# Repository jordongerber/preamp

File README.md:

# Preamp

## Goals

 * Learn Kicad
 * Become familiar with microcontroller programming
  * SPI
  * Shift registers
  * Mux/Demux
  * Controller interrupts
 * Make a bomb preamp
  * See the block diagram in [/preamp-layout/](https://github.com/SlurpyTurts/preamp/tree/master/preamp-layout) for details of the overall design.

## Implementation
* I am planning to use an ESP32 controller as the MCU
* This preamp will implement relay-controlled input and output switching
  * Inputs
    * Some number of single-ended RCA pairs
 	  * 1-2 pairs balanced pairs
    * relays controlled via demux from MCU. Input control via
      * Front panel rotary encoder
      * Front panel capacitive touch sensors
      * IR remote control
      * Because it's an ESP32, I gotta play with network control
 		* Selection remembered when the device is power-cycled
 	* Outputs
 		* 1x single-ended RCA pair
 		* 1x balanced XLR pair
 		* Headphone Amp
 			* Op-amp driven amp will have single-ended output.
 			* Preamp main outputs will be muted when the headphone amp has a device inserted
 			* When headphones are inserted the previous headphone level will be retained
 			* When headphones are unplugged the main output volume will be retained from before insertion
 		* Upon bootup the headphone volume will come in low (previous state not remembered) but not off, TBD
 * Volume control will be implemented via an MDAC controller
 * Selectable gain setting: 0dB or +12dB
 * Power Supply
 	* Separate linear power supplies for analog and digital sections
 		* 5V
 		* +-15V
 * Headphone Amp
 	* Single-ended Op-amp design
 * Tone Controls
 	* Meh. At the moment I don't really care about tone controls on this unit. If I do add them I'd like to have:
 		* Low/high pass loudness controls w/ controllable corner frequency
 		* Parametric upper-midrange control, 2kHz - 5kHz, variable Q, variable gain (-6dB to 0dB)
 		* Parametric lower-midrange control, 200Hz - 500kHz, variable Q, variable gain (-6dB to +2dB)  

## Instructions

* The files in [/preamp-code](https://github.com/SlurpyTurts/preamp/tree/master/preamp-code) can be run in the Arduino IDE. Currently it is configured for an ESP32.
* The schematic & pcb files in [/preamp-layout/preamp-kicad](https://github.com/SlurpyTurts/preamp/tree/master/preamp-layout/preamp-kicad) can be viewed using KiCad. Open the file ```preamp.pro```
* An overview of the schematic layout of this preamp is located at [preamp/preamp-layout/preamp-kicad/preamp.pdf](https://github.com/SlurpyTurts/preamp/blob/master/preamp-layout/preamp-kicad/preamp.pdf)

## References

### Preamp design
 * https://github.com/FutureSharks/preamp-two
 * https://www.muffsy.com/muffsy-relay-input-selector-4.html
 * https://sound-au.com/articles/balanced-io.htm
 * http://www.interfacebus.com/tone-control-3-band-tlo82-opamp-design.html
 * http://www.thatcorp.com/2181-series_Trimmable_Blackmer_IC_Voltage-Controlled_Amplifiers.shtml

### Power Supply design
 * https://www.eleccircuit.com/dual-adjustable-power-supply-circuit-diagram/

### SPI
 * SPI - http://www.circuitbasics.com/basics-of-the-spi-communication-protocol/
 * shift registers for mux - https://www.brainy-bits.com/get-more-inputs-on-your-arduino-by-using-a-shift-register/
 * https://github.com/espressif/arduino-esp32/blob/master/libraries/SPI/examples/SPI_Multiple_Buses/SPI_Multiple_Buses.ino
 * https://github.com/espressif/arduino-esp32/issues/1942
 * https://github.com/MajenkoLibraries/MCP23S17

### Arduino
  * encoder interrupts - http://bristolwatch.com/arduino/arduino2.htm
  * encoder interrupts - https://www.arduino.cc/reference/en/language/functions/external-interrupts/attachinterrupt/
  * flash memory - https://randomnerdtutorials.com/esp32-flash-memory/

### Other
 * Neopixel - https://www.adafruit.com/product/3094

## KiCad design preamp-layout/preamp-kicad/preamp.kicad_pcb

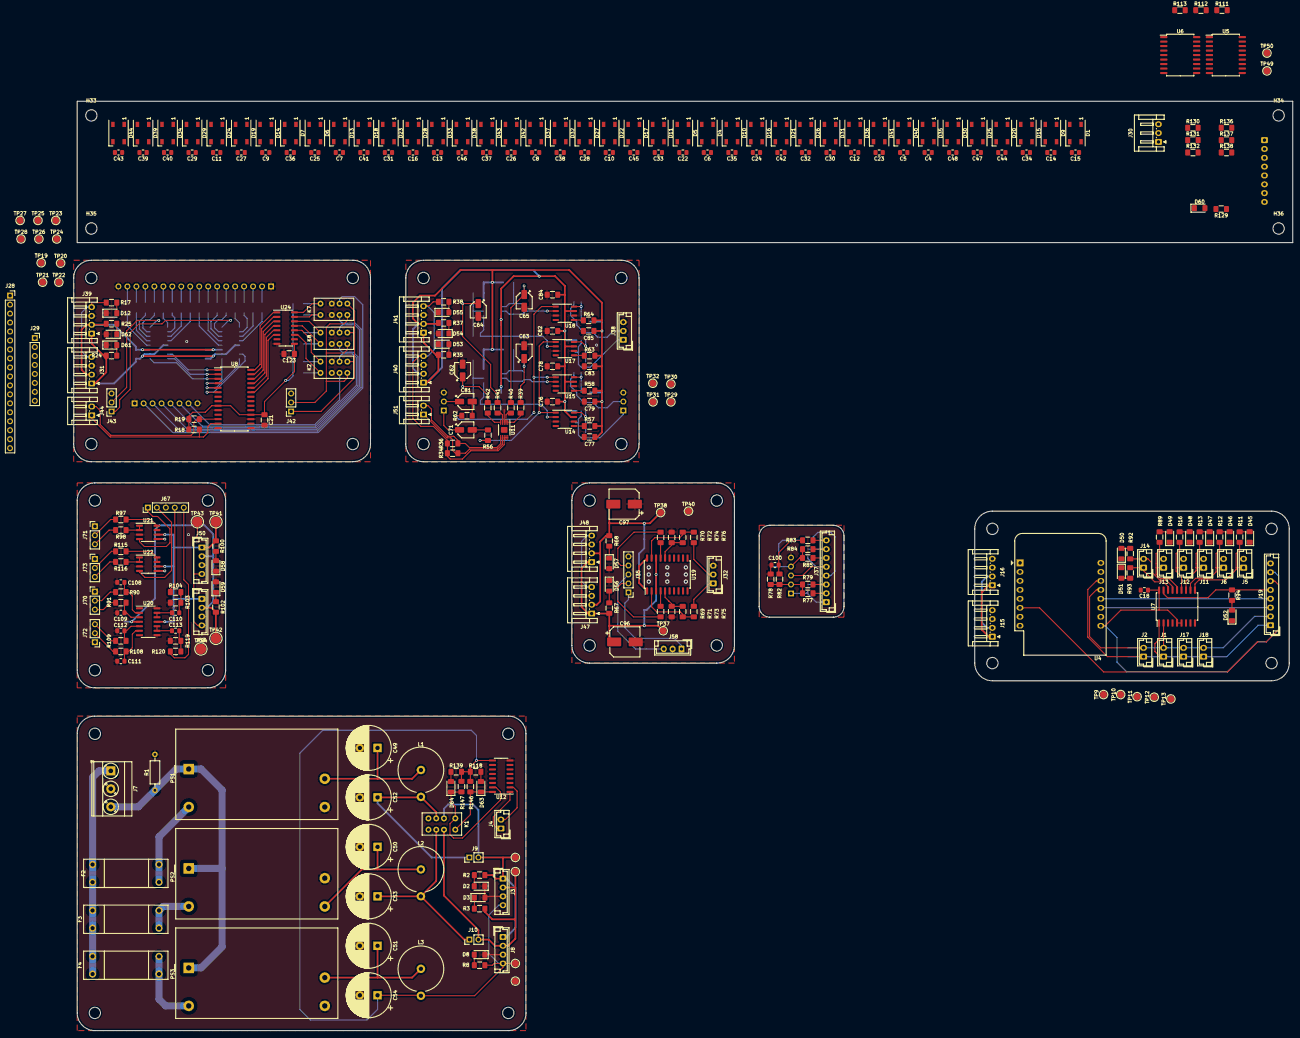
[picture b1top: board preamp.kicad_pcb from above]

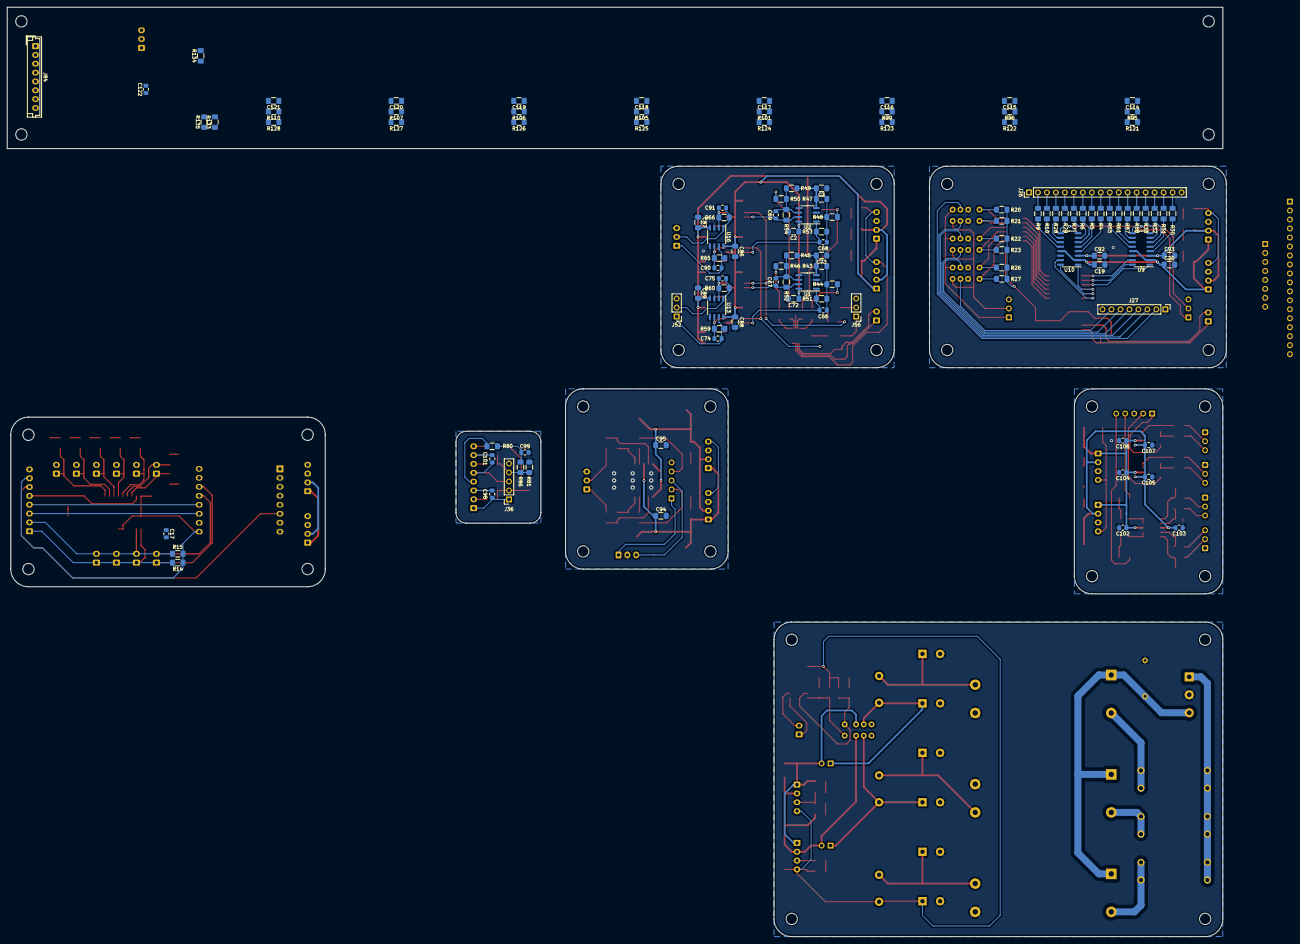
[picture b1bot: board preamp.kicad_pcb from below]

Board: 2 copper layers, 345.0 x 263.0 mm, 461 parts (115 on the bottom side), 245 nets.

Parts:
C2, C3, C19, C20, C21, C72, C73, C76, C77, C78, C79, C82, C83, C84, C85, C86, C87, C88, C89, C92, C93, C94, C95, C114, C115, C116, C117, C118, C119, C120, C121, C123: 0.1uF; C_1206_3216Metric_Pad1.42x1.75mm_HandSolder
C4, C5, C6, C7, C8, C9, C10, C11, C12, C13, C14, C15, C16, C22, C23, C24, C25, C26, C27, C28, C29, C30, C31, C32, C33, C34, C35, C36, C37, C38, C39, C40, C41, C42, C43, C44, C45, C46, C47, C48: 100nF; C_0805_2012Metric_Pad1.15x1.40mm_HandSolder
C17, C18, C66, C67, C68, C69, C102, C103, C104, C105, C106, C107, C122: 0.1uF; C_0805_2012Metric_Pad1.15x1.40mm_HandSolder
C49, C50, C51, C52, C53, C54: 470uF; CP_Radial_D12.5mm_P5.00mm
C62, C63, C64, C65: 2.2uF; CP_Elec_4x5.4
C71, C81: 10uF; CP_Elec_4x5.4
C74, C75, C90, C91: 22pF; C_0805_2012Metric_Pad1.15x1.40mm_HandSolder
C96, C97: 100uF; CP_Elec_8x6.2
C98, C101: 0.022uF; C_0805_2012Metric_Pad1.15x1.40mm_HandSolder
C99, C100: 0.12uF; C_0805_2012Metric_Pad1.15x1.40mm_HandSolder
C108, C109, C111, C112: 470pF; C_0805_2012Metric_Pad1.15x1.40mm_HandSolder
C110, C113: 22uF; C_0805_2012Metric_Pad1.15x1.40mm_HandSolder
D1, D4, D5, D6, D7, D9, D10, D11, D13, D14, D15, D16, D17, D18, D19, D20, D21, D22, D23, D24, D25, D26, D27, D28, D29, D30, D31, D32, D33, D34, D35, D36, D37, D38, D39, D40, D41, D42, D43, D44: WS2812B; LED_WS2812B_PLCC4_5.0x5.0mm_P3.2mm
D2, D3, D53, D54, D56, D57, D58, D59, D61, D62: GREEN; LED_1206_3216Metric_Pad1.42x1.75mm_HandSolder
D8, D12, D45, D46, D47, D48, D49, D50, D51, D52, D55, D60, D63, D64: RED; LED_1206_3216Metric_Pad1.42x1.75mm_HandSolder
F2, F3, F4: 500mA; 01110501Z_3AG
H1, H2, H3, H4, H9, H10, H11, H12, H17, H18, H19, H20, H21, H22, H23, H24, H25, H26, H27, H28, H29, H30, H31, H32, H33, H34, H35, H36: MountingHole; MountingHole_3.2mm_M3
J1, J2, J4, J5, J6, J11, J12, J13, J14, J17, J18: Conn_01x02_Female; JST_EH_B2B-EH-A_1x02_P2.50mm_Vertical
J3, J8, J50, J53: Conn_01x04_Male; JST_EH_B4B-EH-A_1x04_P2.50mm_Vertical
J7: Screw_Terminal_01x03; TerminalBlock_Phoenix_MKDS-3-3-5.08_1x03_P5.08mm_Horizontal
J9, J10: Conn_01x02_Male; PinHeader_1x02_P2.54mm_Vertical
J15, J16, J31, J39, J40, J41, J47, J48: Conn_01x04_Male; JST_EH_S4B-EH_1x04_P2.50mm_Horizontal
J19, J84: Conn_01x08_Female; JST_EH_B8B-EH-A_1x08_P2.50mm_Vertical
J26: Conn_01x18_Male; PinHeader_1x18_P2.54mm_Vertical
J27: Conn_01x08_Male; PinHeader_1x08_P2.54mm_Vertical
J28: Conn_01x18_Female; PinSocket_1x18_P2.54mm_Vertical
J29: Conn_01x08_Female; PinSocket_1x08_P2.54mm_Vertical
J30: Conn_01x03_Female; JST_EH_S3B-EH_1x03_P2.50mm_Horizontal
J32, J38, J58: Conn_01x03_Male; JST_EH_B3B-EH-A_1x03_P2.50mm_Vertical
J35, J67: Conn_01x05_Male; PinHeader_1x05_P2.54mm_Vertical
J36: Conn_01x05_Female; PinSocket_1x05_P2.54mm_Vertical
J37: Conn_01x08_Male; JST_EH_B8B-EH-A_1x08_P2.50mm_Vertical
J42, J43: Conn_01x03_Female; PinSocket_1x03_P2.54mm_Vertical
J44: Conn_01x02_Female; JST_EH_S2B-EH_1x02_P2.50mm_Horizontal
J51: Conn_01x02_Male; JST_EH_S2B-EH_1x02_P2.50mm_Horizontal
J52, J56: Conn_01x03_Male; PinHeader_1x03_P2.54mm_Vertical
J70, J71, J72, J73: XLR3; PinHeader_1x03_P2.54mm_Vertical
K1, K2, K7, K8: G6JU; Relay_DPDT_Omron_G6JU-2P-Y
L1, L2, L3: 150uH; L_Axial_L23.4mm_D12.7mm_P7.62mm_Vertical_Vishay_IHA-203
PS1, PS2: IRM-10-15; Converter_ACDC_MeanWell_IRM-10-xx_THT
PS3: IRM-05-5; Converter_ACDC_MeanWell_IRM-05-xx_THT
R1: 4.7M; R_Axial_DIN0207_L6.3mm_D2.5mm_P10.16mm_Horizontal
R2, R3: 1.3k; R_1206_3216Metric_Pad1.42x1.75mm_HandSolder
R4, R5, R6, R7, R9, R10, R28, R29, R30, R31, R32, R33, R55, R61, R87, R88, R90, R91, R97, R98, R104, R108, R109, R115, R116, R120, R121, R122, R123, R124, R125, R126, R127, R128: 100R; R_1206_3216Metric_Pad1.42x1.75mm_HandSolder
R8, R11, R12, R13, R16, R17, R38, R89, R92, R93, R94, R118, R129, R139: 330R; R_1206_3216Metric_Pad1.42x1.75mm_HandSolder
R14, R15, R18, R19, R24, R25, R34, R35, R36, R37, R67, R68, R77, R85, R100, R102, R111, R113, R133, R135: 1.5k; R_1206_3216Metric_Pad1.42x1.75mm_HandSolder
R20, R21, R22, R23, R26, R27, R69, R70, R146, R147: 51R; R_1206_3216Metric_Pad1.42x1.75mm_HandSolder
R39, R40, R41, R42: 6.34k; R_1206_3216Metric_Pad1.42x1.75mm_HandSolder
R43, R45, R47, R49: 178k; R_1206_3216Metric_Pad1.42x1.75mm_HandSolder
R44, R46, R48, R50: 6.49k; R_1206_3216Metric_Pad1.42x1.75mm_HandSolder
R51, R52, R53, R54: 2k; R_1206_3216Metric_Pad1.42x1.75mm_HandSolder
R56, R59, R60, R62, R65, R66: 20k; R_1206_3216Metric_Pad1.42x1.75mm_HandSolder
R57, R58, R63, R64: 5.1k; R_1206_3216Metric_Pad1.42x1.75mm_HandSolder
R71, R72, R73, R74, R78, R86, R130, R131, R132, R136, R137, R138: 1k; R_1206_3216Metric_Pad1.42x1.75mm_HandSolder
R75, R76: 10R; R_1206_3216Metric_Pad1.42x1.75mm_HandSolder
R79, R84: 9.1k; R_1206_3216Metric_Pad1.42x1.75mm_HandSolder
R80, R81, R82, R83: 3.3k; R_1206_3216Metric_Pad1.42x1.75mm_HandSolder
R95, R96, R99, R101, R105, R106, R107, R110: 1M; R_1206_3216Metric_Pad1.42x1.75mm_HandSolder
R103, R119: 100k; R_1206_3216Metric_Pad1.42x1.75mm_HandSolder
R112, R134: 10k; R_1206_3216Metric_Pad1.42x1.75mm_HandSolder
TP9, TP10, TP11, TP12, TP13, TP19, TP20, TP21, TP22, TP23, TP24, TP25, TP26, TP27, TP28, TP29, TP30, TP31, TP32, TP37, TP38, TP40, TP45, TP46, TP47, TP48, TP49, TP50: TestPoint; TestPoint_Pad_D2.0mm
TP41, TP42, TP43, TP44: TestPoint; TestPoint_Pad_D3.0mm
U1, U2: TL072; SOIC-8_3.9x4.9mm_P1.27mm
U4: WeMos_D1_mini; WEMOS_D1_mini_light
U5, U6, U7: MCP23008T-E_SO; SOIC-18W_7.5x11.6mm_P1.27mm
U8: MCP23017_SO; SOIC-28W_7.5x17.9mm_P1.27mm
U9, U10: DG408DY; SOIC-16_3.9x9.9mm_P1.27mm
U11: DAC5574; MSOP-10-1EP_3x3mm_P0.5mm_EP1.68x1.88mm
U12, U24: ULN2003; SOIC-16_3.9x9.9mm_P1.27mm
U13, U16: NJM2068M; SOP-8_3.9x4.9mm_P1.27mm
U14, U15, U17, U18: THAT2181; SO-8_3.9x4.9mm_P1.27mm
U19: TPA6120; SOIC-20W_7.5x12.8mm_P1.27mm
U20: THAT1280; SOIC-14_3.9x8.7mm_P1.27mm
U21, U22: THAT1646; SOIC-8_3.9x4.9mm_P1.27mm

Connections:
+3.3V: C17.1, TP12.1, U4.8
+5V: C4.1, C5.2, C6.1, C7.2, C8.1, C9.2, C10.1, C11.2, C12.1, C13.2, C14.1, C15.2, C16.1, C18.1, C21.1, C22.2, C23.1, C24.2, C25.1, C26.2, C27.1, C28.2, C29.1, C30.2, C31.1, C32.2, C33.1, C34.2, C35.1, C36.2, C37.1, C38.2, C39.1, C40.2, C41.1, C42.2, C43.1, C44.2, C45.1, C46.2, C47.1, C48.2, C54.1, C122.1, C123.1, D1.1, D4.1, D5.1, D6.1, D7.1, D9.1, D10.1, D11.1, D13.1, D14.1, D15.1, D16.1, D17.1, D18.1, D19.1, D20.1, D21.1, D22.1, D23.1, D24.1, D25.1, D26.1, D27.1, D28.1, D29.1, D30.1, D31.1, D32.1, D33.1, D34.1, D35.1, D36.1, D37.1, D38.1, D39.1, D40.1, D41.1, D42.1, D43.1, D44.1, J3.4, J8.4, J15.4, J16.4, J19.7, J30.1, J31.4, J39.4, J40.4, J41.4, J47.4, J48.4, J50.4, J53.4, J84.7, L3.2, R8.1, R14.1, R15.1, R17.1, R18.1, R19.1, R20.1, R21.1, R22.1, R23.1, R26.1, R27.1, R34.1, R36.1, R38.1, R95.2, R96.2, R99.2, R101.2, R105.2, R106.2, R107.2, R110.2, R111.1, R113.1, R118.1, R129.1, R130.1, R131.1, R132.1, R133.1, R135.1, R136.1, R137.1, R138.1, R139.1, R146.1, R147.1, TP11.1, TP21.1, TP31.1, TP43.1, TP47.1, TP49.1, U4.9, U5.18, U6.3, U6.18, U7.5, U7.6, U7.18, U8.9, U8.16, U8.18, U11.8, U11.9, U11.10, U12.9, U24.9
+15V: C2.1, C19.1, C20.1, C72.1, C76.1, C78.1, C82.1, C84.1, C86.1, C88.1, C94.1, C96.1, C102.1, C104.1, C106.1, J3.1, J8.1, J9.2, J15.1, J16.1, J31.1, J39.1, J40.1, J41.1, J47.1, J48.1, J50.1, J53.1, K1.7, R2.1, R24.2, R35.1, R67.1, R100.1, TP9.1, TP19.1, TP29.1, TP37.1, TP41.1, TP45.1, U1.8, U2.8, U9.2, U9.13, U10.2, U10.13, U13.8, U14.7, U15.7, U16.8, U17.7, U18.7, U19.3, U19.18, U20.11, U21.6, U22.6
-15V: C3.2, C73.2, C77.2, C79.2, C83.2, C85.2, C87.2, C89.2, C92.1, C93.1, C95.1, C97.2, C103.2, C105.2, C107.2, J3.2, J8.2, J10.2, J15.2, J16.2, J31.2, J39.2, J40.2, J41.2, J47.2, J48.2, J50.2, J53.2, K1.2, R3.1, R25.1, R37.1, R43.2, R45.2, R47.2, R49.2, R57.2, R58.2, R63.2, R64.2, R68.1, R102.1, TP10.1, TP20.1, TP30.1, TP38.1, TP42.1, TP46.1, U1.4, U2.4, U9.3, U10.3, U13.4, U16.4, U19.1, U19.20, U20.4, U21.5, U22.5
/DC_PWR SUPPLY/+15: C52.1, J9.1, K1.6, L1.2
/DC_PWR SUPPLY/-15: C53.1, J10.1, K1.3, L2.2
/DC_PWR SUPPLY/AC_HOT: F2.2, F3.2, F4.2, J7.1
/DC_PWR SUPPLY/AC_N: J7.3, PS1.1, PS2.1, PS3.1, R1.1
/DC_PWR SUPPLY/STBY_CTRL_1: D63.1, K1.1, R146.2, U12.16
/DC_PWR SUPPLY/STBY_CTRL_2: D64.1, K1.8, R147.2, U12.15
/DC_PWR SUPPLY/STBY_RST: J4.2, J14.1, R93.1, U7.16, U12.2
/DC_PWR SUPPLY/STBY_SET: J4.1, J14.2, R92.1, U7.15, U12.1
/IO/A_IN_1_L: J26.2, J28.2, R9.2
/IO/A_IN_1_R: J26.10, J28.10, R55.2
/IO/A_IN_2_L: J26.3, J28.3, R10.2
/IO/A_IN_2_R: J26.11, J28.11, R61.2
/IO/A_IN_3_L: J26.4, J28.4, R28.2
/IO/A_IN_3_R: J26.12, J28.12, R87.2
/IO/A_IN_4_L: J26.5, J28.5, R29.2
/IO/A_IN_4_R: J26.13, J28.13, R88.2
/IO/A_IN_5_L: J26.6, J28.9, J67.4, R7.2, R104.1
/IO/A_IN_5_R: J26.14, J28.17, J67.5, R33.2, R120.1
/IO/A_OUT_1_L: J27.2, J29.2, K7.3
/IO/A_OUT_1_R: J27.3, J29.3, K7.6
/IO/A_OUT_2_L: J27.4, J29.4, J67.1, K8.3, U21.4
/IO/A_OUT_2_R: J27.5, J29.5, J67.2, K8.6, U22.4
/MCU/ENC_INT: J19.3, J84.4, U4.11, U6.8
/MCU/GP0: J5.1, R11.1, U7.10
/MCU/GP1: J6.1, R12.1, U7.11
/MCU/GP2: J11.1, R13.1, U7.12
/MCU/GP3: J12.1, R16.1, U7.13
/MCU/GP4: J13.1, R89.1, U7.14
/MCU/~FP_RST: J19.5, J84.5, R94.1, R112.2, R134.2, U7.17
/SCL: J1.1, J2.1, J17.1, J18.1, J19.1, J44.2, J51.2, J84.2, R14.2, R19.2, R36.2, R113.2, R135.2, U4.14, U5.2, U6.2, U7.1, U8.12, U11.6
/SDA: J1.2, J2.2, J17.2, J18.2, J19.2, J44.1, J51.1, J84.1, R15.2, R18.2, R34.2, R111.2, R133.2, U4.13, U5.1, U6.1, U7.2, U8.13, U11.7
/Volume Control/A_IN_L: R56.1, U14.1, U17.1
/Volume Control/A_IN_R: R62.1, U15.1, U18.1
/Volume Control/DAC_A: R39.2, U11.1
/Volume Control/DAC_B: R40.2, U11.2
/Volume Control/DAC_C: R41.2, U11.4
/Volume Control/DAC_D: R42.2, U11.5
/Volume Control/GAIN_CTRL_1_L: C68.1, R53.1, U2.1, U17.2
/Volume Control/GAIN_CTRL_1_R: C69.1, R54.1, U2.7, U18.2
/Volume Control/GAIN_CTRL_2_L: C66.1, R51.1, U1.1, U14.2
/Volume Control/GAIN_CTRL_2_R: C67.1, R52.1, U1.7, U15.2
/front panel/FP_INT_SW: J19.4, J84.3, U4.12, U5.8
/front panel/FP_LED_DT: D1.4, J19.6, J30.2, J84.6, U4.6
/front panel/SEL_CLK: R131.2, U6.10
/front panel/SEL_DT: R130.2, U6.11
/front panel/SEL_SW: R132.2, U6.12
/front panel/SW_IN_1: R121.2, U5.10
/front panel/SW_IN_2: R122.2, U5.11
/front panel/SW_IN_3: R123.2, U5.12
/front panel/SW_IN_4: R124.2, U5.13
/front panel/SW_IN_5: R125.2, U5.14
/front panel/SW_MUTE: R126.2, U5.15
/front panel/SW_OUT_1: R127.2, U5.16
/front panel/SW_OUT_2: R128.2, U5.17
/front panel/VOL_CLK: R137.2, U6.13
/front panel/VOL_DT: R136.2, U6.14
/front panel/VOL_SW: R138.2, U6.15
/headphone amp/Headphone Crossfeed/SW_L_OUT_1: C98.2, J37.3, R79.1
/headphone amp/Headphone Crossfeed/SW_L_OUT_2: J37.4, R80.1
/headphone amp/Headphone Crossfeed/SW_R_OUT_1: C101.2, J37.7, R84.1
/headphone amp/Headphone Crossfeed/SW_R_OUT_2: J37.8, R83.1
/headphone amp/Headphone Crossfeed/VR_L_OUT: J37.2, R77.1
/headphone amp/Headphone Crossfeed/VR_R_OUT: J37.6, R85.1
/headphone amp/IN_L: C90.1, C98.1, J35.1, J36.1, J37.1, J38.1, J58.1, R65.1, U16.7
/headphone amp/IN_R: C91.1, C101.1, J35.3, J36.3, J37.5, J38.2, J58.3, R66.1, U16.1
/headphone amp/OUT_L: J32.1, R75.1
/headphone amp/OUT_R: J32.2, R76.1
/headphone amp/xfeed_out_l: J35.2, J36.2, R69.2, R77.2, R78.1, R79.2, R82.2
/headphone amp/xfeed_out_r: J35.4, J36.4, R70.2, R81.2, R84.2, R85.2, R86.1
/input selector/A_IN_6_L: J26.7, R6.2
/input selector/A_IN_6_R: J26.15, R32.2
/input selector/A_IN_7_L: J26.8, R5.2
/input selector/A_IN_7_R: J26.16, R31.2
/input selector/A_IN_8_L: J26.9, R4.2
/input selector/A_IN_8_R: J26.17, R30.2
/input selector/A_IN_L: C74.1, J42.1, J52.1, K2.4, K7.4, K8.4, R59.1, U13.7
/input selector/A_IN_R: C75.1, J42.2, J52.2, K2.5, K7.5, K8.5, R60.1, U13.1
/input selector/A_OUT_3_L: J27.6, K2.3
/input selector/A_OUT_3_R: J27.7, K2.6
/input selector/A_OUT_L: C71.1, J43.1, J56.1, U10.8
/input selector/A_OUT_R: C81.1, J43.2, J56.2, U9.8
/input selector/IN_L_SEL_A0: TP23.1, U8.4, U10.1
/input selector/IN_L_SEL_A1: TP24.1, U8.5, U10.16
/input selector/IN_L_SEL_A2: TP25.1, U8.6, U10.15
/input selector/IN_R_SEL_A0: TP26.1, U8.3, U9.1
/input selector/IN_R_SEL_A1: TP27.1, U8.2, U9.16
/input selector/IN_R_SEL_A2: TP28.1, U8.1, U9.15
/input selector/OUT_1_R+: K7.8, R21.2, U24.15
/input selector/OUT_1_S+: K7.1, R20.2, U24.16
/input selector/OUT_2_R+: K8.8, R23.2, U24.13
/input selector/OUT_2_S+: K8.1, R22.2, U24.14
/input selector/OUT_3_R+: K2.8, R27.2, U24.11
/input selector/OUT_3_S+: K2.1, R26.2, U24.12
/input selector/RLY_1_R+: U8.27, U24.2
/input selector/RLY_1_S+: U8.28, U24.1
/input selector/RLY_2_R+: U8.25, U24.4
/input selector/RLY_2_S+: U8.26, U24.3
/input selector/RLY_3_R+: U8.23, U24.6
/input selector/RLY_3_S+: U8.24, U24.5
GND: C2.2, C3.1, C4.2, C5.1, C6.2, C7.1, C8.2, C9.1, C10.2, C11.1, C12.2, C13.1, C14.2, C15.1, C16.2, C17.2, C18.2, C19.2, C20.2, C21.2, C22.1, C23.2, C24.1, C25.2, C26.1, C27.2, C28.1, C29.2, C30.1, C31.2, C32.1, C33.2, C34.1, C35.2, C36.1, C37.2, C38.1, C39.2, C40.1, C41.2, C42.1, C43.2, C44.1, C45.2, C46.1, C47.2, C48.1, C49.2, C50.2, C51.2, C52.2, C53.2, C54.2, C62.2, C63.2, C64.2, C65.2, C72.2, C73.1, C76.2, C77.1, C78.2, C79.1, C82.2, C83.1, C84.2, C85.1, C86.2, C87.1, C88.2, C89.1, C92.2, C93.2, C94.2, C95.2, C96.2, C97.1, C99.2, C100.2, C102.2, C103.1, C104.2, C105.1, C106.2, C107.1, C108.2, C109.1, C111.2, C112.1, C114.2, C115.2, C116.2, C117.2, C118.2, C119.2, C120.2, C121.2, C122.2, C123.2, D1.3, D2.1, D3.2, D4.3, D5.3, D6.3, D7.3, D8.1, D9.3, D10.3, D11.3, D12.1, D13.3, D14.3, D15.3, D16.3, D17.3, D18.3, D19.3, D20.3, D21.3, D22.3, D23.3, D24.3, D25.3, D26.3, D27.3, D28.3, D29.3, D30.3, D31.3, D32.3, D33.3, D34.3, D35.3, D36.3, D37.3, D38.3, D39.3, D40.3, D41.3, D42.3, D43.3, D44.3, D45.1, D46.1, D47.1, D48.1, D49.1, D50.1, D51.1, D52.1, D53.1, D54.2, D55.1, D56.1, D57.2, D58.1, D59.2, D60.1, D61.1, D62.2, J3.3, J5.2, J6.2, J7.2, J8.3, J11.2, J12.2, J13.2, J15.3, J16.3, J19.8, J26.1, J26.18, J27.1, J27.8, J28.1, J28.18, J29.1, J29.8, J30.3, J31.3, J32.3, J35.5, J36.5, J38.3, J39.3, J40.3, J41.3, J42.3, J43.3, J47.3, J48.3, J50.3, J52.3, J53.3, J56.3, J58.2, J67.3, J70.1, J71.1, J72.1, J73.1, J84.8, K2.2, K2.7, K7.2, K7.7, K8.2, K8.7, PS1.3, PS2.4, PS3.3, R1.2, R71.2, R72.2, R78.2, R86.2, R103.2, R119.2, TP13.1, TP22.1, TP32.1, TP40.1, TP44.1, TP48.1, TP50.1, U1.3, U1.5, U2.3, U2.5, U4.10, U5.3, U5.4, U5.5, U5.9, U6.4, U6.5, U6.9, U7.3, U7.4, U7.9, U8.10, U8.15, U8.17, U9.14, U10.14, U11.3, U12.8, U13.3, U13.5, U14.3, U14.6, U15.3, U15.6, U16.3, U16.5, U17.3, U17.6, U18.3, U18.6, U20.8, U20.14, U21.3, U22.3, U24.8
unnamed: C49.1, L1.1, PS1.4
unnamed: C50.1, L2.1, PS2.3
unnamed: C51.1, L3.1, PS3.4
unnamed: C62.1, R42.1, R44.2
unnamed: C63.1, R39.1, R46.2
unnamed: C64.1, R41.1, R48.2
unnamed: C65.1, R40.1, R50.2
unnamed: C66.2, R43.1, R44.1, R51.2, U1.2
unnamed: C67.2, R45.1, R46.1, R52.2, U1.6
unnamed: C68.2, R47.1, R48.1, R53.2, U2.2
unnamed: C69.2, R49.1, R50.1, R54.2, U2.6
unnamed: C71.2, R56.2
unnamed: C74.2, R59.2, U13.6, U14.8
unnamed: C75.2, R60.2, U13.2, U15.8
unnamed: C81.2, R62.2
unnamed: C90.2, R65.2, U16.6, U17.8
unnamed: C91.2, R66.2, U16.2, U18.8
unnamed: C99.1, R80.2, R81.1
unnamed: C100.1, R82.1, R83.2
unnamed: C108.1, R90.1, U20.2
unnamed: C109.2, R91.1, U20.3
unnamed: C110.1, U20.12, U20.13
unnamed: C110.2, R103.1, R104.2
unnamed: C111.1, R108.1, U20.6
unnamed: C112.2, R109.1, U20.5
unnamed: C113.1, U20.9, U20.10
unnamed: C113.2, R119.1, R120.2
unnamed: C114.1, R95.1, R121.1
unnamed: C115.1, R96.1, R122.1
unnamed: C116.1, R99.1, R123.1
unnamed: C117.1, R101.1, R124.1
unnamed: C118.1, R105.1, R125.1
unnamed: C119.1, R106.1, R126.1
unnamed: C120.1, R107.1, R127.1
unnamed: C121.1, R110.1, R128.1
unnamed: D1.2, D9.4
unnamed: D2.2, R2.2
unnamed: D3.1, R3.2
unnamed: D4.2, D5.4
unnamed: D6.2, D7.4
unnamed: D8.2, R8.2
unnamed: D4.4, D10.2
unnamed: D10.4, D16.2
unnamed: D11.2, D17.4
unnamed: D5.2, D11.4
unnamed: D12.2, R17.2
unnamed: D6.4, D13.2
unnamed: D13.4, D18.2
unnamed: D14.2, D19.4
unnamed: D7.2, D14.4
unnamed: D15.2, D20.4
unnamed: D9.2, D15.4
unnamed: D16.4, D21.2
unnamed: D17.2, D22.4
unnamed: D18.4, D23.2
unnamed: D19.2, D24.4
unnamed: D20.2, D25.4
unnamed: D21.4, D26.2
unnamed: D22.2, D27.4
unnamed: D23.4, D28.2
unnamed: D24.2, D29.4
unnamed: D25.2, D30.4
unnamed: D26.4, D31.2
unnamed: D27.2, D32.4
unnamed: D28.4, D33.2
unnamed: D29.2, D34.4
unnamed: D30.2, D35.4
unnamed: D31.4, D36.2
unnamed: D32.2, D37.4
unnamed: D33.4, D38.2
unnamed: D34.2, D39.4
unnamed: D35.2, D40.4
unnamed: D36.4, D41.2
unnamed: D37.2, D42.4
unnamed: D38.4, D43.2
unnamed: D39.2, D44.4
unnamed: D40.2, D41.4
unnamed: D42.2, D43.4
unnamed: D45.2, R11.2
unnamed: D46.2, R12.2
unnamed: D47.2, R13.2
unnamed: D48.2, R16.2
unnamed: D49.2, R89.2
unnamed: D50.2, R92.2
unnamed: D51.2, R93.2
unnamed: D52.2, R94.2
unnamed: D53.2, R35.2
unnamed: D54.1, R37.2
unnamed: D55.2, R38.2
unnamed: D56.2, R67.2
unnamed: D57.1, R68.2
unnamed: D58.2, R100.2
unnamed: D59.1, R102.2
unnamed: D60.2, R129.2
unnamed: D61.2, R24.1
unnamed: D62.1, R25.2
unnamed: D63.2, R118.2
unnamed: D64.2, R139.2
unnamed: F2.1, PS1.2
unnamed: F3.1, PS2.2
unnamed: F4.1, PS3.2
unnamed: J70.2, R90.2
unnamed: J70.3, R91.2
unnamed: J71.2, R97.1
unnamed: J71.3, R98.1
unnamed: J72.2, R108.2
unnamed: J72.3, R109.2
unnamed: J73.2, R115.1
unnamed: J73.3, R116.1
unnamed: R4.1, U10.4
unnamed: R5.1, U10.5
unnamed: R6.1, U10.6
unnamed: R7.1, U10.7
unnamed: R9.1, U10.12
unnamed: R10.1, U10.11
unnamed: R28.1, U10.10
unnamed: R29.1, U10.9
unnamed: R30.1, U9.4
unnamed: R31.1, U9.5
unnamed: R32.1, U9.6
unnamed: R33.1, U9.7
unnamed: R55.1, U9.12
unnamed: R57.1, U14.5
unnamed: R58.1, U15.5
unnamed: R61.1, U9.11
unnamed: R63.1, U17.5
unnamed: R64.1, U18.5
unnamed: R69.1, U19.4
unnamed: R70.1, U19.17
unnamed: R71.1, R73.2, U19.5
unnamed: R72.1, R74.2, U19.16
unnamed: R73.1, R75.2, U19.2
unnamed: R74.1, R76.2, U19.19
unnamed: R87.1, U9.10
unnamed: R88.1, U9.9
unnamed: R97.2, U21.7, U21.8
unnamed: R98.2, U21.1, U21.2
unnamed: R112.1, U5.6
unnamed: R115.2, U22.7, U22.8
unnamed: R116.2, U22.1, U22.2
unnamed: R134.1, U6.6

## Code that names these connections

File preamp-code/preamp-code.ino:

/*
 * When configured for DOIT ESP32, GPIO pins are assigned as the pin number (GPIO4 is pin 4)
 * When configured for ESP8266 NodeMCU, GPIO pins are assigned as the pin label according to the silkscreen on the PCB (defining a pin by D4 correlates to D4 on the board) 
 * currently configured for DOIT ESP32 DEVKIT V1 board
 * 
 */

#include <EEPROM.h>
#include "Preamp.h"
#include <SPI.h>

SPIClass IO_Expand(VSPI);

//preamp IO ports
#define NUM_INPUTS 6
#define NUM_OUTPUTS 1

//assigning EEPROM locations
#define EEPROM_SIZE 4
#define VOLUME_STORE 0
#define INPUT_STORE 1
#define OUTPUT_STORE 2
#define MUTE_STORE 3

//assigning encoder pins
#define VOL_CLK 27
#define VOL_DT 14
#define VOL_SW 13

#define SEL_CLK 33
#define SEL_DT 25
#define SEL_SW 26

#define NUM_LEDS 60
#define LED_PIN 16

Preamp preamp(NUM_INPUTS, NUM_OUTPUTS, new Encoder(VOL_CLK, VOL_DT, VOL_SW), new Encoder(SEL_CLK, SEL_DT, SEL_SW), new Adafruit_NeoPixel(60, 16, NEO_GRB + NEO_KHZ800));

enum Actions{vol_up, vol_down, vol_set, sel_next, sel_prev, sel_set, toggle_mute};
Actions action;

int vol, input, output = 0; //for assigning values to the preamp

//------------------------INPUT SWITCHES------------------------
//this will eventually be replaced by an SPI connection with an additional flag line to say that somethign has changed. CHIP NUMBER ______
Switch inputSelectSwitch[NUM_INPUTS];
const int inputSwitches[] = {15, 2};

//------------------------DELAYS------------------------
const int debounce_delay = 20; //microseconds. This is used in the encoder interrupt methods
const int volume_select_delay = 10; //milliseconds. This is used in the main loop switch case
const int io_select_delay = 100; //milliseconds. This is used in the main loop switch case

//------------------------INTERRUPTS------------------------
//this is required for interrupts to work in ESP8266 / ESP32, unable to find reliable documentation as to why. This specifies that the routine is put in RAM
void ICACHE_RAM_ATTR SELECT_CW_INTERRUPT(), SELECT_CCW_INTERRUPT(), SELECT_SWITCH_INTERRUPT();
void ICACHE_RAM_ATTR VOLUME_CW_INTERRUPT(), VOLUME_CCW_INTERRUPT(),VOLUME_SW_INTERRUPT();

void ICACHE_RAM_ATTR SELECT_INPUT_INTERRUPT();

bool CLK_set, DT_set = false;

void setup(){

  EEPROM.begin(EEPROM_SIZE);

  //pinMode(5, OUTPUT);
  //IO_Expand.begin(18, 23, 19, 5);
  
  //initializing preamp from EEPROM stored values
  preamp.setVolume(EEPROM.read(VOLUME_STORE));
  preamp.setInput(EEPROM.read(INPUT_STORE));
  preamp.setOutput(EEPROM.read(OUTPUT_STORE));
  preamp.setMute(EEPROM.read(MUTE_STORE));

  //attach interrupts to all controls going in to MCU (encoders, switches, IR, wifi)
  attachInterrupt(digitalPinToInterrupt(preamp.get_selector_encoder_CLKPIN()), SELECT_CW_INTERRUPT, CHANGE);
  attachInterrupt(digitalPinToInterrupt(preamp.get_selector_encoder_DTPIN()), SELECT_CCW_INTERRUPT, CHANGE);
  attachInterrupt(digitalPinToInterrupt(preamp.get_selector_encoder_SWPIN()), SELECT_SWITCH_INTERRUPT, RISING);
  
  attachInterrupt(digitalPinToInterrupt(preamp.get_volume_encoder_CLKPIN()), VOLUME_CW_INTERRUPT, CHANGE);
  attachInterrupt(digitalPinToInterrupt(preamp.get_volume_encoder_DTPIN()), VOLUME_CCW_INTERRUPT, CHANGE);
  attachInterrupt(digitalPinToInterrupt(preamp.get_volume_encoder_SWPIN()), VOLUME_SWITCH_INTERRUPT, RISING);

  for(int i = 0; i < NUM_INPUTS; i++){
    inputSelectSwitch[i].configure(inputSwitches[i], HIGH);
    attachInterrupt(digitalPinToInterrupt(inputSelectSwitch[i].getPin()), SELECT_INPUT_INTERRUPT, RISING);
  }
 
  preamp.startup();
  
}

void loop(){

  if(preamp.status_change){
    switch(action){
      case vol_up:
        preamp.volume_up();
        EEPROM.write(VOLUME_STORE, preamp.getVolume());
        EEPROM.commit();
        delay(volume_select_delay);
        break;
      case vol_down:
        preamp.volume_down();
        EEPROM.write(VOLUME_STORE, preamp.getVolume());
        EEPROM.commit();
        delay(volume_select_delay);
        break;
      case vol_set:
        preamp.setVolume(vol);
        EEPROM.write(VOLUME_STORE, preamp.getVolume());
        EEPROM.commit();
        delay(volume_select_delay);
        break;
      case sel_prev:
        preamp.select_previous();
        EEPROM.write(INPUT_STORE, preamp.getInput());
        EEPROM.commit();
        delay(io_select_delay);
        break;
      case sel_next:
        preamp.select_next();
        EEPROM.write(INPUT_STORE, preamp.getInput());
        EEPROM.commit();
        delay(io_select_delay);
        break;
      case sel_set:
        preamp.setInput(input);
        EEPROM.write(INPUT_STORE, preamp.getInput());
        EEPROM.commit();
        delay(io_select_delay);
        break;
      case toggle_mute:
        preamp.toggle_mute();
        EEPROM.write(MUTE_STORE, preamp.isMute());
        EEPROM.commit();
        delay(io_select_delay);
        break;
    }
    
    preamp.status_change = false;
  }
}


//--------------------------SELECT ENCODER--------------------------

void SELECT_CW_INTERRUPT(){
  delayMicroseconds(debounce_delay);
  if(digitalRead(preamp.get_selector_encoder_CLKPIN()) != CLK_set){
    CLK_set = !CLK_set;
    if(CLK_set && !DT_set){
      action = sel_next;
      preamp.status_change = true;
    }
  }
}

void SELECT_CCW_INTERRUPT(){
  delayMicroseconds(debounce_delay);
  if(digitalRead(preamp.get_selector_encoder_DTPIN()) != DT_set){
    DT_set = !DT_set;
    if(DT_set && !CLK_set){
      action = sel_prev;
      preamp.status_change = true;
    }
  }
}

void SELECT_SWITCH_INTERRUPT(){
//  delayMicroseconds(debounce_delay);
//  if(digitalRead(preamp.get_selector_encoder_SWPIN()) == LOW){
    action = toggle_mute;
    preamp.status_change = true;
//  }
}


//---------------------VOLUME ENCODER--------------------------

void VOLUME_CW_INTERRUPT(){
  delayMicroseconds(debounce_delay);
  if(digitalRead(preamp.get_volume_encoder_CLKPIN()) != CLK_set){
    CLK_set = !CLK_set;
    if(CLK_set && !DT_set){
      action = vol_up;
      preamp.status_change = true;
    }
  }
}

void VOLUME_CCW_INTERRUPT(){
  delayMicroseconds(debounce_delay);
  if(digitalRead(preamp.get_volume_encoder_DTPIN()) != DT_set){
    DT_set = !DT_set;
    if(DT_set && !CLK_set){
      action = vol_down;
      preamp.status_change = true;
    }
  }
}

void VOLUME_SWITCH_INTERRUPT(){
//  delayMicroseconds(debounce_delay);
//  if(digitalRead(preamp.get_volume_encoder_SWPIN()) == LOW){
    action = toggle_mute;
    preamp.status_change = true;
//  }
}



//--------------------------CAPACITIVE SWITCHES--------------------------

void SELECT_INPUT_INTERRUPT(){
  for(int i = 0; i < NUM_INPUTS; i++){
    if(inputSelectSwitch[i].is_pressed())
      input = i;
      action = sel_set;
      preamp.status_change = true;
      break;
  }
}

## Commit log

2019-12-08 added long-press functionality to encoder.h, implemented in preamp-code.ino
2019-12-09 created Switch class to encapsulate functions of the encoder. Updated Encoder.h accordingly.
2019-12-09 initial readme update
2019-12-09 readme update
2019-12-09 gitignore
2019-12-10 Moved kicad project and files to a new location. Updated readme. Added block diagram of digital / analog circuitry
2019-12-10 removed bak files from /preamp-layout/preamp-kicad
2019-12-13 BOM skeleton added. gitignore updated to ignore schematic bak files. General work done on the schematic layout.
2019-12-13 minor readme updates
2019-12-13 readme references update. preamp-code updated to implement interrupts for encoder input. Layout general updates
2019-12-14 general layout work
2019-12-21 Started filling in BOM. Encoder.h changed by removing number of rotary / switch positions from constructor. preamp-code.ino completely redone to implement Preamp.h.
2019-12-21 Updated references in readme. Changed preamp bootup routine. Minor refactoring of preamp.h and preamp-code.ino
2019-12-24 Replaced FastLED with Adafruit_Neopixel library for controlling Neopixel display strip because FastLED and HW SPI don't play well together. Continuing to walk through SPI.
2019-12-24 Working with SPI, in particular the MCP23S17 library. The plan is to deconstruct this and use general, more basic SPI communications with all chips attached to the ESP32 (master).
2019-12-25 Update README.md
    added reference to preamp.pdf
2019-12-31 IO layout cleanup
    Changed location of bal/unbal buffers from selector board to daughter board. Generalized IO PCB to accept daughter boards, not specific to connector type or bal/unbal. The idea is that as many unbala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
2019-12-31 Encoder, LED, front panel update
    Removed hierarchical sheets for encoders, moved encoders to main sheet. Added switches for output select on front panel sheet. Added LEDs on front panel sheet but only as a symbol, only two instances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
2019-12-31 Tone Control update
    Generated analog tone controls controlled either by pots mounted on the front panel or encoders mounted on the front panel that communicate to the tone control board via SPI.
2020-01-10 Updates
    Minor Readme updates.
    Schematic:
    - Bus connector lines replaced single wire connectors
    - Title block populated.
    - Power Supply updates.
    - Preliminary Front Panel.
2020-01-13 Added preliminary gain stage
    Gain stage added with choice of 6db or 12db gain. Cleaned up Gain stage IO pins on preamp sheet. Broke out volume ctrl to its own board, updated accordingly. Minor routing changes on preamp sheet.
2020-01-16 VCA gain control
    Removed MDAC volume control and gain stage, replaced with VCA gain stage.
2020-01-16 VCA update
    Added connectors, notes. Redraw of schematic pdf.
2020-01-16 Power conn cleanup
    5V and 15V cleaned up on all sheets
2020-01-16 Sheet cleanup
2020-01-19 Created component library, changed connector pinouts
    Project library was created for this project to house custom parts, starting with Omron relay. 15V supply conn output changed so that pin 1 remains +15V, but pin 2 is now common and pin 3 is now -15V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
    Implemented new schematic symbol for relays, general sheet cleanup. Removed MISO from IO selector board.
2020-01-19 Library update, MCU config
    preliminary config of MCU with newly created ESP32 symbol in project library.
2020-01-19 Layout update
    New project plot, added pinout link for ESP32
2020-01-21 Grounds cleaned up, initial refdes numbering, error correction
    GNDA, GNDS, GNDD, GND all combined to GND. No point in having separate grounds for this design.
    Initial refdes numbering done using auto numbering feature. Error detection run and multple issues found which prompted Ground fix, as well as learning the disconnected pins require a 'no connection'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
    Error correction also prompted the AC power connector symbol change to a plug to attempt to fix an error regarding 'driving' the circuit....more work to be done on error analysis.
2020-01-21 Error correction, PWR_FLAG
    PWR_FLAG works like this:
    https://forum.kicad.info/t/errtype-3-pin-connected-to-some-others-pins-but-no-pin-to-drive-it/10946
    Added this in power supplies to get rid of warnings that came up during ERC.
2020-01-21 Power Supply Conn Update
    Added screw terminals to AC schematic, fixed pin conn numbers on PSU sheets
2020-01-24 Refdes update, U20 mod
    I believe that the component symbol for MCP4902 has been incorrectly constructed int he standard Kicad libraries. Pin 9 (~SHDN) is an output per the standard library, however I am fairly certain it i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
2020-01-24 AC PCB Update
    Removed Switch symbol from PCB, moved to main sheet. Started playing with footprint assignment. Other minor updates.
2020-01-24 Initial Footprint Assignment
    Assigned footprints to SMT resistors, pin headers, screw terminals, LEDs, DIP-8 ICs
2020-01-27 BOM update
    Minor changes to schematic, value changes and footprint entry. BOM updated with parts sourcing
2020-02-02 power headers updated, slight BOM update
    changed footprint on all 5V, +-15V to JST B2B / B3B connectors. All male conns now.
2020-02-02 Transformer specification
    updated schematic, BOM with power transformer info. Other minor schematic tweaks.
2020-02-02 screw terminal update
    AC power conn update to implement ground. Moved BOM to html file format for web view, not sure if I like it like this but wanted to try it.
2020-02-02 BOM formatting
2020-02-02 Added front panel LED sheet. BOM update. Front panel PCA work
    other minor changes like LED color assignments, etc
2020-02-05 LED resistor update
    In the process of reviewing layouts and associated parts sourcing, I realized that I had incorrectly calculated the resistors needed for the power supply LEDs on all boards. Updated BOM and schematic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
2020-02-05 Initial Review
    Reviewing schematic, comparing to references and filling in BOM to match schematics. Updating footprints in the process as well.
2020-02-05 Added License
2020-02-19 AC ground conn update
2020-02-19 Update headphone_amp.sch
    first draft of headphone amp
2020-02-19 Update preamp.pdf
    new plot uploaded
2020-02-26 Headphone Amp Crossfeed Implementation - using the CMOY modified Linkwitz High Z crossfeed design as a basis.
2020-02-27 BOM Update
    Realized that after saving as an HTML document, the file I was manipulating in OpenOffice would be lost once closed. I updated the .odf doc to match what was in the html file, then overwrote the html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
2020-03-01 Incorporated Standby Relay
    The Relay shown on the AC Input page is meant to control the +/-15V supply. The coil is controlled by two pins on the esp32 MCU. The 5V supply will be active at all times. I think the working conditi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
2020-03-02 BOM Update
    parts added to BOM, connector cleanup. Stopping point before renumbering refdes in a more intelligent way.
2020-03-02 Schematic Updates
    Updated pin connections for DAC, footprint updates, MCU connections.
2020-03-03 Schematic Redesignation
    Regenerated RefDes for all parts, updated BOM accordingly and perfomred check on values, RefDes present from schematic to BOM. Value changes, BOM filled in as a result.
2020-03-04 Added Bypass Capacitors
    0.1uF caps added at power supplies of all ICs
2020-03-04 Footprint assignment updates
2020-03-06 voltage regulator update
    regulators used in 15V supply changed from LM7805, LM7905 to LM7815, LM7915
2020-03-06 Headphone Amp Update
    Removed IC buffer on headphone amp schematic. Reconfigured connectors to crossfeed board so that input/output can be easily jumpered.
2020-03-12 Footprint updates
    Footprint creation of relay, ESP32
2020-03-16 Op Amp change up
    Changed DAC output buffer to quad TL074 instead of separate TL072 ICs. Changed signal path ICs from generic TL072 to NJM2068M. Updated footprints, BOM, schematic.
2020-03-17 balanced IO update
    other general minor updates
2020-03-20 Conn / Pin Updates
    Updated cable headers, pin names, MCU conn layout. MCP4902 changeout for custom symbol.
2020-03-21 Power Supply Update
    Grounding made more clear, tied to chassis on AC board. Pins renamed. Aligned with AC wall power convention. General cleanup.
2020-03-22 Schematic layout updates
    schematic optimization. Also implemented encoders with surrounding circuitry (self-contained on encoder board)
2020-03-23 Sheet cleanup
    pin names reassigned, standardized. Organized sheets to reduce clutter, increase readability.
2020-03-23 I2C init commit
    Changed design from using SPI interface to I2C interface, with exception of front LED array (SPI).
2020-03-23 File Cleanup
    Removed deprecated files
2020-03-23 SPI init commit
    branching master off to SPI branch. Thinking that I2C will be the preferred communication interface so I will probably merge the I2C_Communication branch to master eventually, wanted to separate the 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
2020-03-23 BOM Update
2020-03-25 Minor Updates
    Moved headphone jack to amp pcb. I2C pin updates. Added caps to LED light strip. Added 0.1uF caps to all ICs.
2020-03-25 BOM check
    Updated BOM to match schematic
2020-03-28 woops
    to merge with I2C
2020-03-28 Test branch combine (MCU changes)
    Incorporated the changes made in the Test branch (can't stash using GitHub Desktop, I forgot to pull before I started making changes to the I2C thus the Test branch was created)
    This includes adding an MCP23017 to the MCU board for IO expansion (flags), adding the pinouts for using an ESP8266 to the existing ESP32 pinout (so that either MCU could be used)
2020-03-28 MCU cleanup
    removed separate header schematic symbols for MCU mounting because that was dumb. Updated ESP32 footprint. Played around with pcb layout even though I'm not close to ready for that yet, just wanted t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
2020-03-29 MCU Update
    Changed ICs used in MCU, reviewed data sheets and updated design of MCU schematic accordingly. Created schematic symbols for ICs.
    Screwed up branches again....wish I could delete this stupid branch. Going to make these same changes to I2C branch now.
2020-03-29 RefDes Update
    Re-ran refdes assignment, updated BOM accordingly.
2020-04-12 Prelim PCB layout
    Work done to lay out PCBs. Saving in anticipation of creating branch with a different input switching topology.
2020-04-20 Periodic backup
    Extensive changes as a result of PCB layout phase.
2020-05-03 PCB layout
    trying a different layout for the gain stage board, this serves as a reference point.
2020-05-04 Balanced in/out update
    Created THAT1646, THAT1280 schematic symbols an implemented in the balanced IO daughter card. Various layout updates as well, this is WIP.
2020-05-24 PCB layout
2020-05-26 PCB layout update, front panel and LED restructure
    Restructure of capacitive buttons. Restructure of MCU schematic. Moved LEDs to front panel sheet. Front panel and MCU initial PCB layout. 8 bit DAC update (grounded address pins). DAC connection rena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
2020-05-30 PCB layout updates, Power supply consolidation
    Combined power supply boards. More PCB layout. PCB net assignment. Added mounting holes to boards. Front panel control / display layout. Various footprint updates / changes.
2020-05-30 Power supply filter Implementation
    Added pi filter on output of DC supplies. PCB layout update on the power supply board.
2020-06-01 MCU update
2020-11-21 many changes made, too long ago to remember
2026-05-19 KiCad Version Migration
    Clean up: migrate to newer KiCad filename format, remove legacy files
